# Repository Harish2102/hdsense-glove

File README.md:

<!-- markdownlint-disable MD041 -->

# HDSense Glove

A high-density 32×32 pressure-sensing glove for prosthetics and haptic feedback

*Johns Hopkins University · Advanced Instruments and Systems · Fall 2024*
*Advised by Dr. Nitish Thakor and Arik Slepyan · Neuroengineering and Biomedical Instrumentation Lab*

---

## Overview

The HDSense Glove maps the full tactile surface of a hand using a **32×32 TDMA sensor array** - 1,024 individual pressure points per glove - streaming real-time contact data over serial. Designed for prosthetic hands, robotic manipulation, and human-computer interaction.

**Key specs:**

- 1,024 pressure sensors per glove (32×32 grid)
- **1000 Hz** frame rate, **20ms** latency
- **88% accuracy** detecting objects via compressed sensing
- **18× faster** than traditional raster scanning (Slepyan et al., 2024)
- Teensy 4.1 microcontroller, low-power flex-PCB design

---

## PCB Design

The glove uses a custom flex-PCB shaped to the anatomy of an average male hand (220mm length). Copper traces follow natural glove cuts with a flexible thumb extension. 32 row output pins are driven sequentially via TDMA, with a 5-bit MUX selecting across 32 columns - reducing 1,024 connections to a single analog readout channel.

Left: KiCad flex-PCB layout shaped to the left hand geometry | Right: 32×32 sensor pixel map with finger and palm zones

The PCB was designed in KiCad with separate left-hand (LH) and right-hand (RH) variants. KiCad source files: [`hardware/LH/`](hardware/LH/) and [`hardware/RH/`](hardware/RH/)

---

## Firmware

`firmware/tdma_32x32_foot.ino` - compiled for **Teensy 4.1**

Performs a full 32×32 raster scan per loop using TDMA, outputs all 1,024 values as a comma-separated serial stream per frame. Uses `FASTRUN` and `digitalWriteFast` for maximum scan speed.

```cpp
for (int i = 0; i < 32; i++) {       // activate row
  for (int j = 0; j < 32; j++) {     // step through mux columns
    values[idx++] = analogRead(A0);  // read pressure
  }
}
```

---

## Project Poster

Full project poster - includes KiCad PCB rendering (Fig. 3) and MATLAB sensor heatmap visualization (Fig. 4)

---

## Docs

| Document | Description |
| -------- | ----------- |
| [Final Pitch Deck](docs/HDSense%20Glove%20Final%20Pitch.pdf) | Product pitch and system overview |
| [Project Poster](docs/Harish_Poster_Final.pdf) | Full project summary poster |

---

Harish Balasubramanian · Johns Hopkins University

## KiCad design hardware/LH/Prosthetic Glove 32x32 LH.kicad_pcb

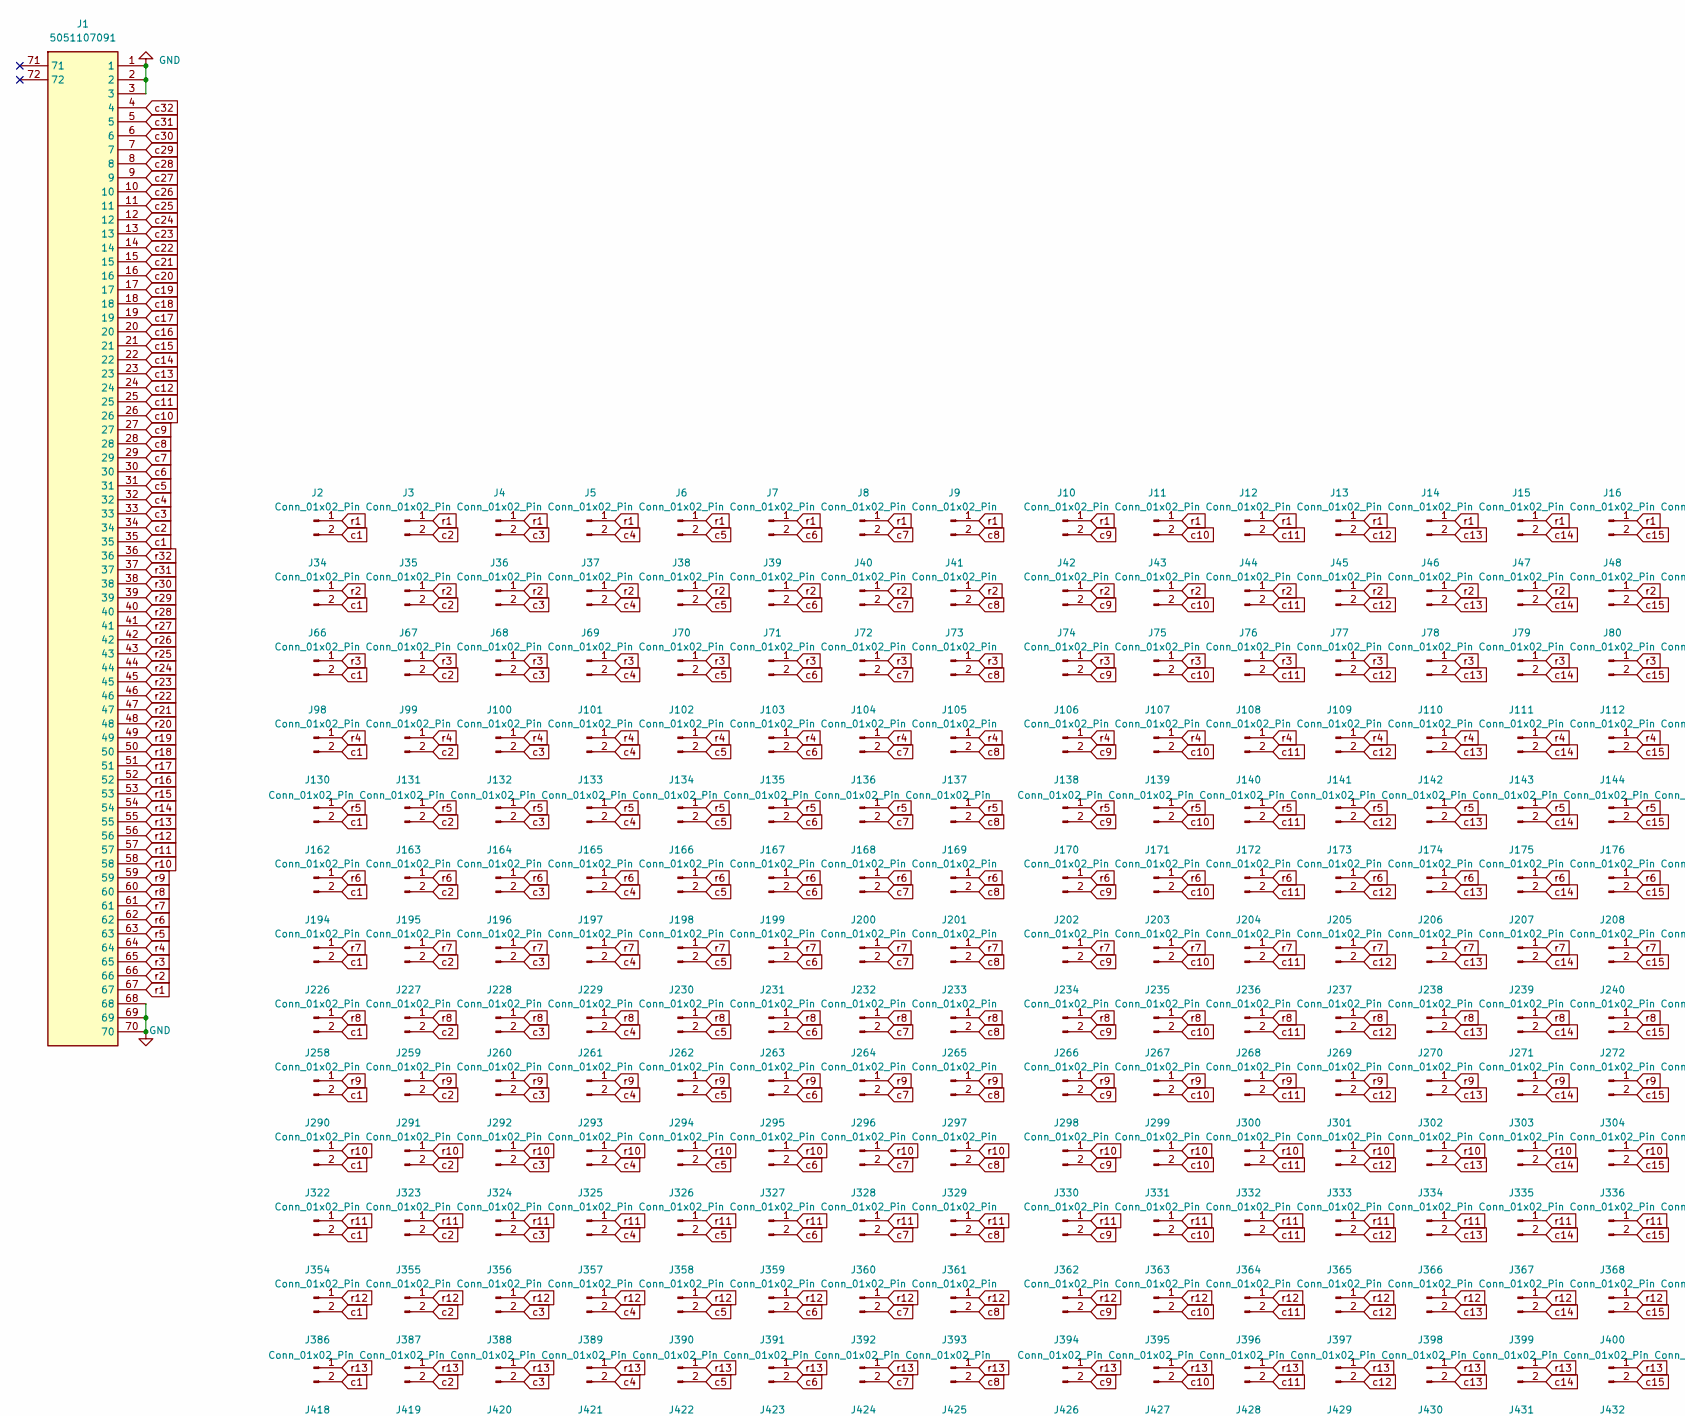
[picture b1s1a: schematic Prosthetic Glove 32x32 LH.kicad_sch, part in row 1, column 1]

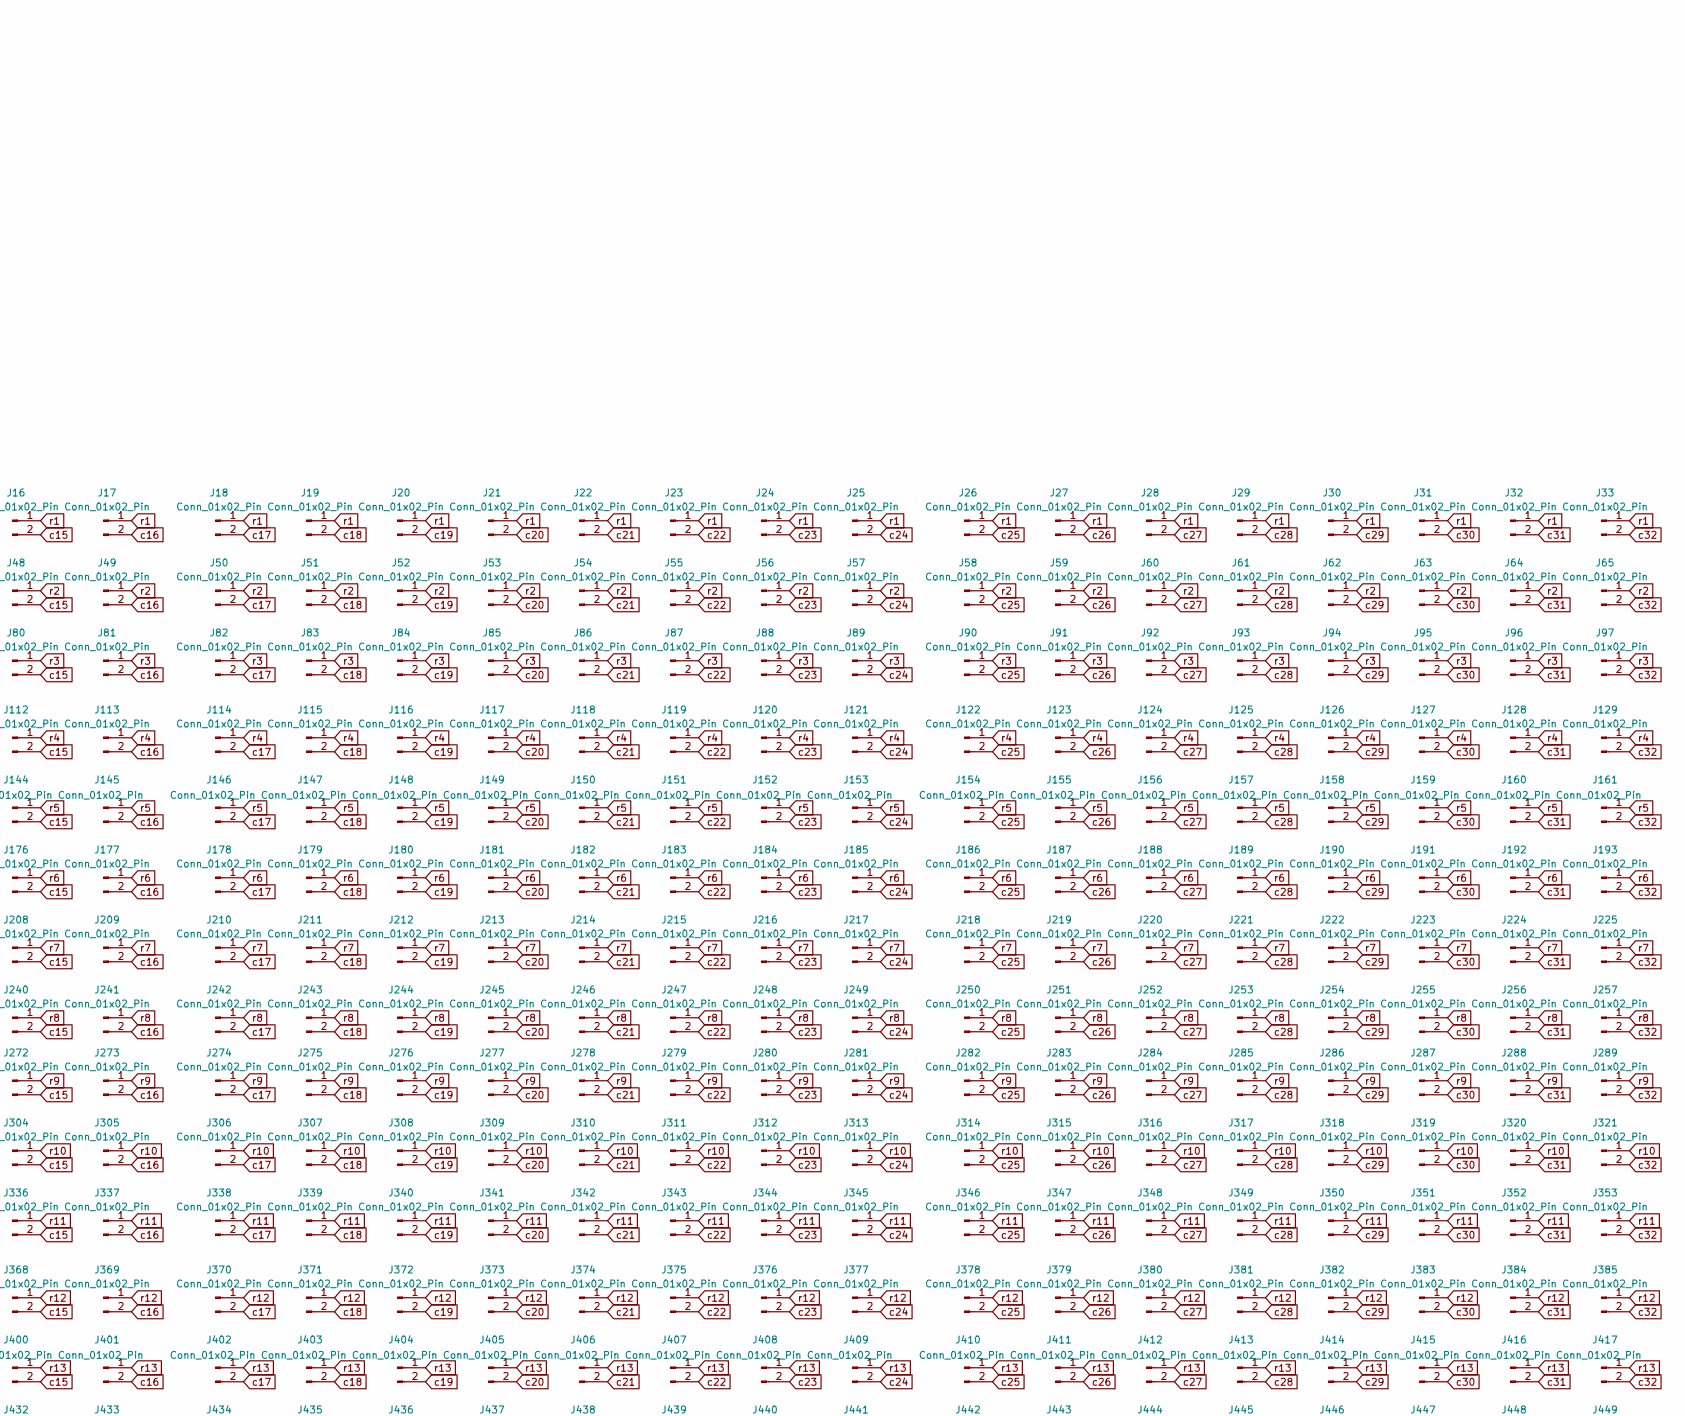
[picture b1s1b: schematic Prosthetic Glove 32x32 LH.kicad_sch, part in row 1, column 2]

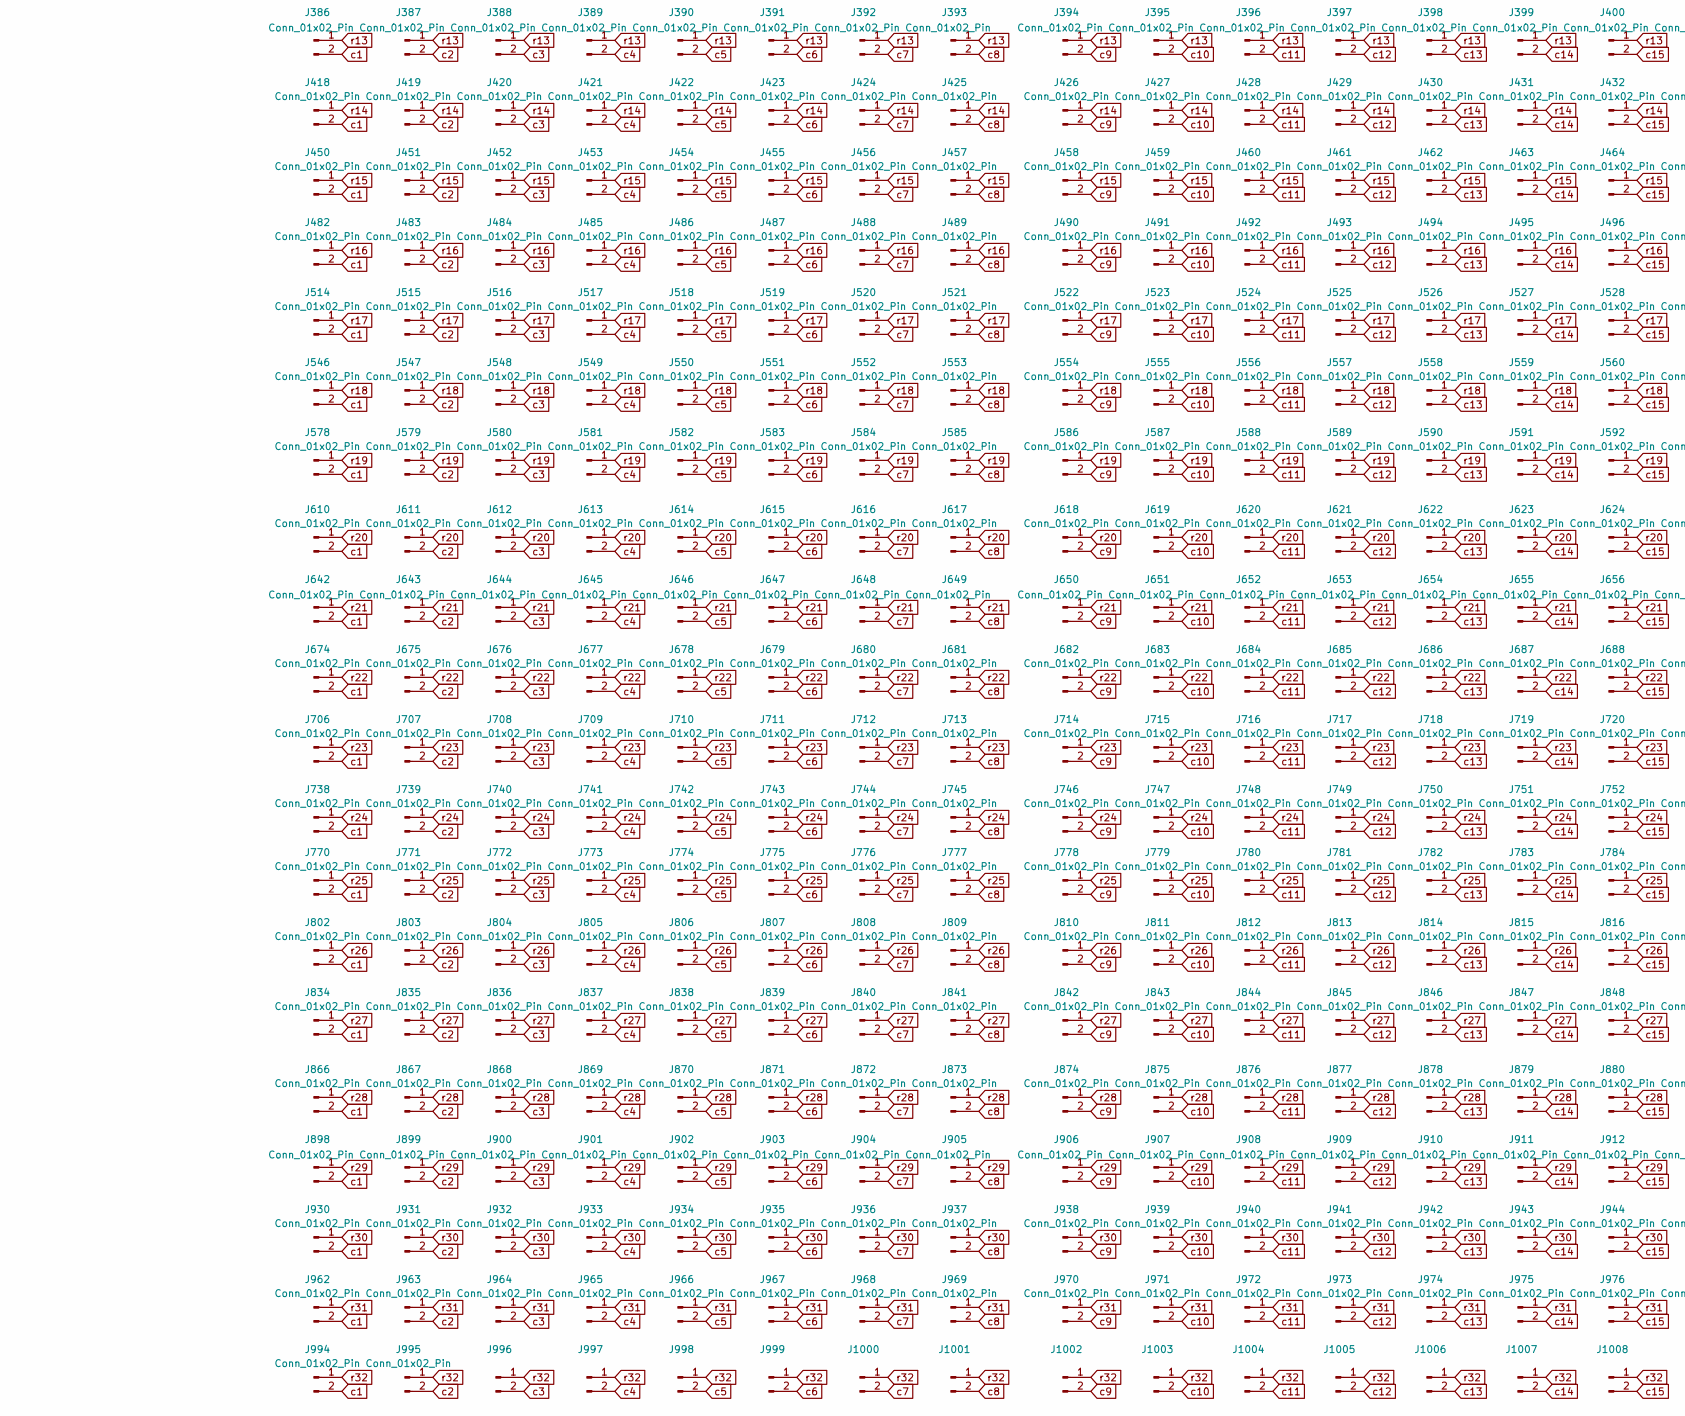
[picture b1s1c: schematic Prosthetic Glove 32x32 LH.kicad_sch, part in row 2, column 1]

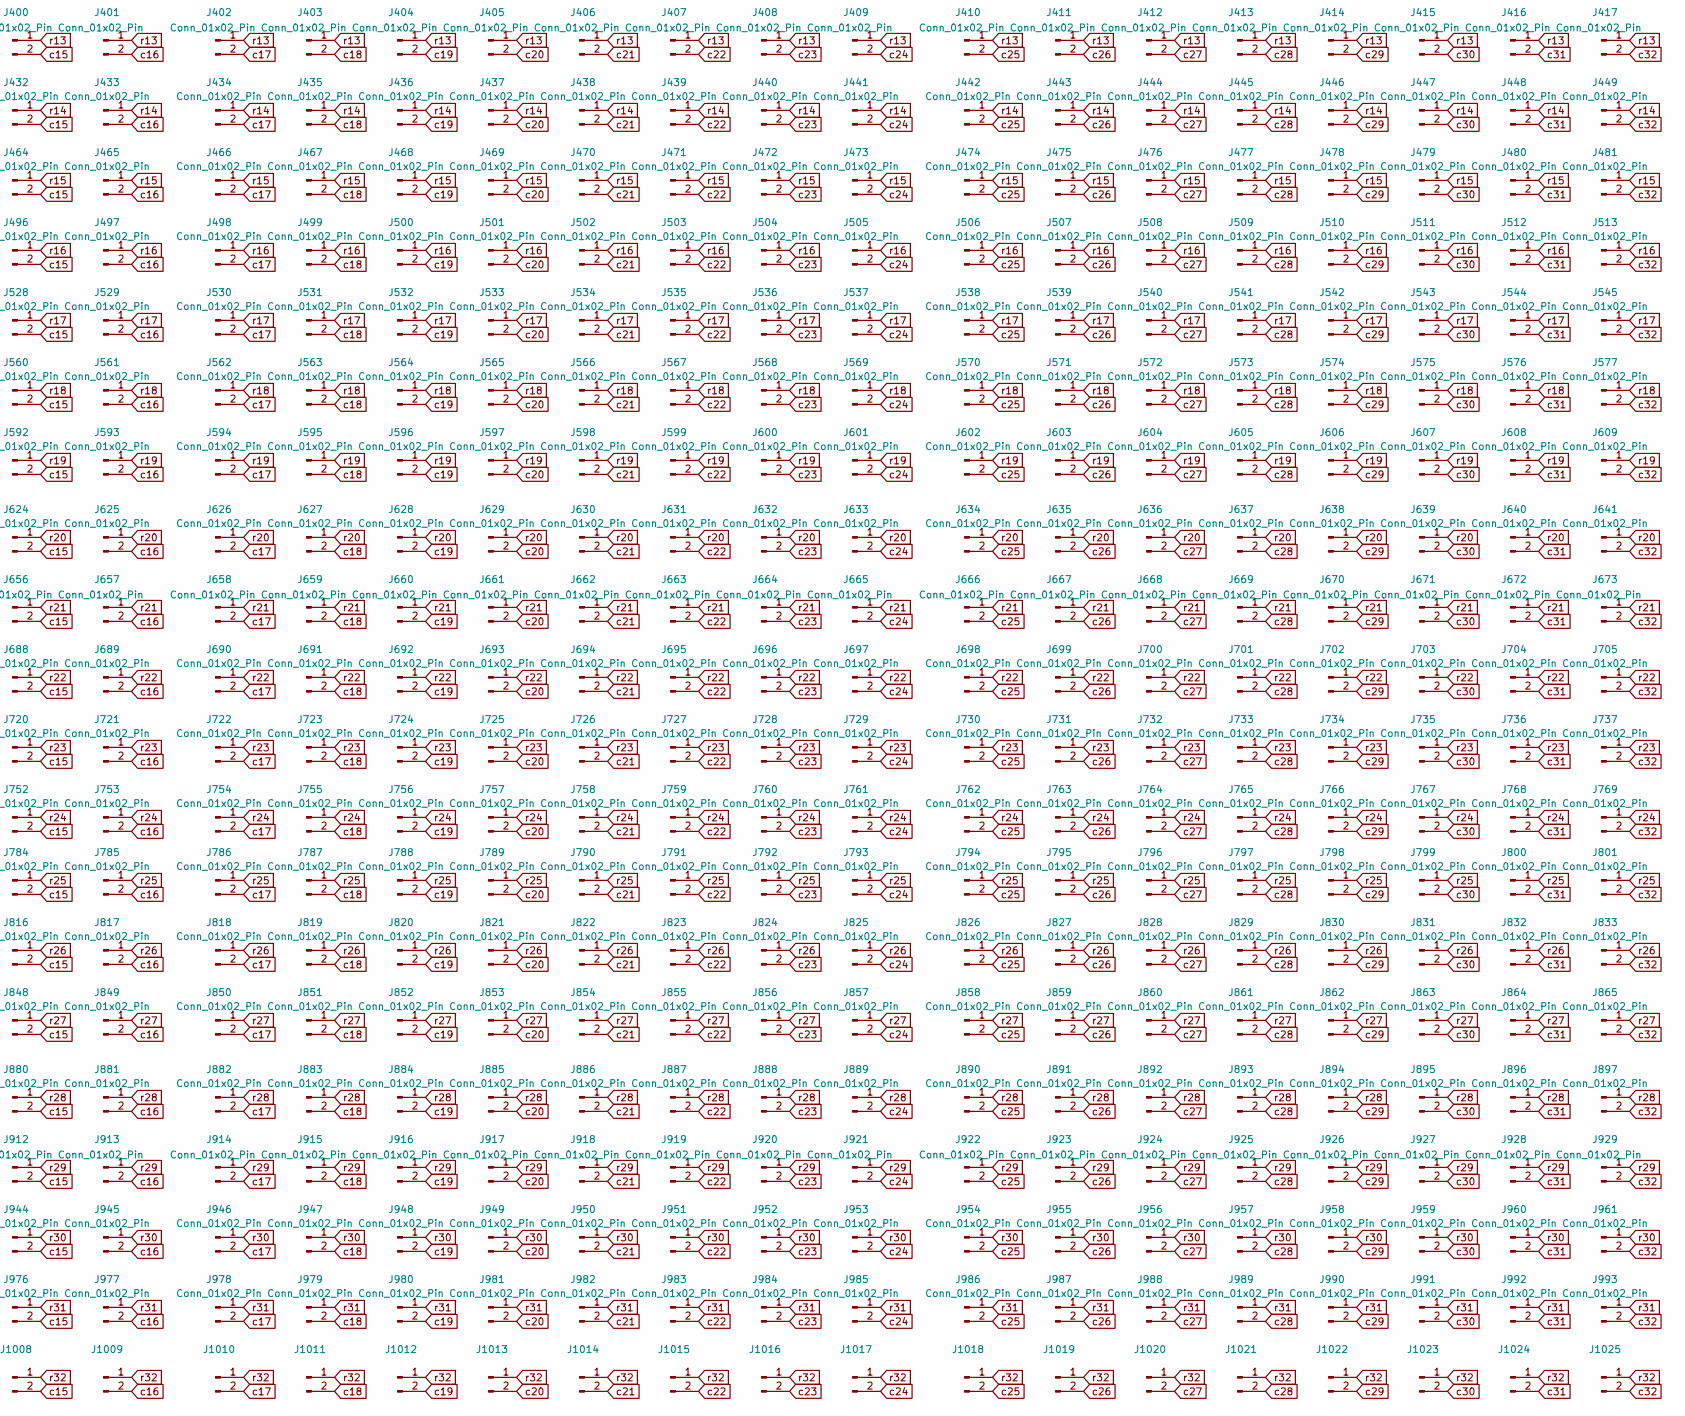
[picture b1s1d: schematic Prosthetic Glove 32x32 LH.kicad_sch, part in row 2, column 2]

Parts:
J1: 5051107091; 70_pos_0.5mm_FPC; Manufacturer_Part_Number 5051107091
J2, J3, J4, J5, J6, J7, J8, J9, J10, J11, J12, J13, J14, J15, J16, J17, J18, J19, J20, J21, J22, J23, J24, J25, J26, J27, J28, J29, J30, J31, J32, J33, J34, J35, J36, J37, J38, J39, J40, J41, J42, J43, J44, J45, J46, J47, J48, J49, J50, J51, J52, J53, J54, J55, J56, J57, J58, J59, J60, J61, J62, J63, J64, J65, J66, J67, J68, J69, J70, J71, J72, J73, J74, J75, J76, J77, J78, J79, J80, J81, J82, J83, J84, J85, J86, J87, J88, J89, J90, J91, J92, J93, J94, J95, J96, J97, J98, J99, J100, J101, J102, J103, J104, J105, J106, J107, J108, J109, J110, J111, J112, J113, J114, J115, J116, J117, J118, J119, J120, J121, J122, J123, J124, J125, J126, J127, J128, J129, J130, J131, J132, J133, J134, J135, J136, J137, J138, J139, J140, J141, J142, J143, J144, J145, J146, J147, J148, J149, J150, J151, J152, J153, J154, J155, J156, J157, J158, J159, J160, J161, J162, J163, J164, J165, J166, J167, J168, J169, J170, J171, J172, J173, J174, J175, J176, J177, J178, J179, J180, J181, J182, J183, J184, J185, J186, J187, J188, J189, J190, J191, J192, J193, J194, J195, J196, J197, J198, J199, J200, J201, J202, J203, J204, J205, J206, J207, J208, J209, J210, J211, J212, J213, J214, J215, J216, J217, J218, J219, J220, J221, J222, J223, J224, J225, J226, J227, J228, J229, J230, J231, J232, J233, J234, J235, J236, J237, J238, J239, J240, J241, J242, J243, J244, J245, J246, J247, J248, J249, J250, J251, J252, J253, J254, J255, J256, J257, J258, J259, J260, J261, J262, J263, J264, J265, J266, J267, J268, J269, J270, J271, J272, J273, J274, J275, J276, J277, J278, J279, J280, J281, J282, J283, J284, J285, J286, J287, J288, J289, J290, J291, J292, J293, J294, J295, J296, J297, J298, J299, J300, J301, J302, J303, J304, J305, J306, J307, J308, J309, J310, J311, J312, J313, J314, J315, J316, J317, J318, J319, J320, J321, J322, J323, J324, J325, J326, J327, J328, J329, J330, J331, J332, J333, J334, J335, J336, J337, J338, J339, J340, J341, J342, J343, J344, J345, J346, J347, J348, J349, J350, J351, J352, J353, J354, J355, J356, J357, J358, J359, J360, J361, J362, J363, J364, J365, J366, J367, J368, J369, J370, J371, J372, J373, J374, J375, J376, J377, J378, J379, J380, J381, J382, J383, J384, J385, J386, J387, J388, J389, J390, J391, J392, J393, J394, J395, J396, J397, J398, J399, J400, J401, J402, J403, J404, J405, J406, J407, J408, J409, J410, J411, J412, J413, J414, J415, J416, J417, J418, J419, J420, J421, J422, J423, J424, J425, J426, J427, J428, J429, J430, J431, J432, J433, J434, J435, J436, J437, J438, J439, J440, J441, J442, J443, J444, J445, J446, J447, J448, J449, J450, J451, J452, J453, J454, J455, J456, J457, J458, J459, J460, J461, J462, J463, J464, J465, J466, J467, J468, J469, J470, J471, J472, J473, J474, J475, J476, J477, J478, J479, J480, J481, J482, J483, J484, J485, J486, J487, J488, J489, J490, J491, J492, J493, J494, J495, J496, J497, J498, J499, J500, J501, J502, J503, J504, J505, J506, J507, J508, J509, J510, J511, J512, J513, J514, J515, J516, J517, J518, J519, J520, J521, J522, J523, J524, J525, J526, J527, J528, J529, J530, J531, J532, J533, J534, J535, J536, J537, J538, J539, J540, J541, J542, J543, J544, J545, J546, J547, J548, J549, J550, J551, J552, J553, J554, J555, J556, J557, J558, J559, J560, J561, J562, J563, J564, J565, J566, J567, J568, J569, J570, J571, J572, J573, J574, J575, J576, J577, J578, J579, J580, J581, J582, J583, J584, J585, J586, J587, J588, J589, J590, J591, J592, J593, J594, J595, J596, J597, J598, J599, J600, J601, J602, J603, J604, J605, J606, J607, J608, J609, J610, J611, J612, J613, J614, J615, J616, J617, J618, J619, J620, J621, J622, J623, J624, J625, J626, J627, J628, J629, J630, J631, J632, J633, J634, J635, J636, J637, J638, J639, J640, J641, J642, J643, J644, J645, J646, J647, J648, J649, J650, J651, J652, J653, J654, J655, J656, J657, J658, J659, J660, J661, J662, J663, J664, J665, J666, J667, J668, J669, J670, J671, J672, J673, J674, J675, J676, J677, J678, J679, J680, J681, J682, J683, J684, J685, J686, J687, J688, J689, J690, J691, J692, J693, J694, J695, J696, J697, J698, J699, J700, J701, J702, J703, J704, J705, J706, J707, J708, J709, J710, J711, J712, J713, J714, J715, J716, J717, J718, J719, J720, J721, J722, J723, J724, J725, J726, J727, J728, J729, J730, J731, J732, J733, J734, J735, J736, J737, J738, J739, J740, J741, J742, J743, J744, J745, J746, J747, J748, J749, J750, J751, J752, J753, J754, J755, J756, J757, J758, J759, J760, J761, J762, J763, J764, J765, J766, J767, J768, J769, J770, J771, J772, J773, J774, J775, J776, J777, J778, J779, J780, J781, J782, J783, J784, J785, J786, J787, J788, J789, J790, J791, J792, J793, J794, J795, J796, J797, J798, J799, J800, J801, J802, J803, J804, J805, J806, J807, J808, J809, J810, J811, J812, J813, J814, J815, J816, J817, J818, J819, J820, J821, J822, J823, J824, J825, J826, J827, J828, J829, J830, J831, J832, J833, J834, J835, J836, J837, J838, J839, J840, J841, J842, J843, J844, J845, J846, J847, J848, J849, J850, J851, J852, J853, J854, J855, J856, J857, J858, J859, J860, J861, J862, J863, J864, J865, J866, J867, J868, J869, J870, J871, J872, J873, J874, J875, J876, J877, J878, J879, J880, J881, J882, J883, J884, J885, J886, J887, J888, J889, J890, J891, J892, J893, J894, J895, J896, J897, J898, J899, J900, J901, J902, J903, J904, J905, J906, J907, J908, J909, J910, J911, J912, J913, J914, J915, J916, J917, J918, J919, J920, J921, J922, J923, J924, J925, J926, J927, J928, J929, J930, J931, J932, J933, J934, J935, J936, J937, J938, J939, J940, J941, J942, J943, J944, J945, J946, J947, J948, J949, J950, J951, J952, J953, J954, J955, J956, J957, J958, J959, J960, J961, J962, J963, J964, J965, J966, J967, J968, J969, J970, J971, J972, J973, J974, J975, J976, J977, J978, J979, J980, J981, J982, J983, J984, J985, J986, J987, J988, J989, J990, J991, J992, J993, J994, J995, J996, J997, J998, J999, J1000, J1001, J1002, J1003, J1004, J1005, J1006, J1007, J1008, J1009, J1010, J1011, J1012, J1013, J1014, J1015, J1016, J1017, J1018, J1019, J1020, J1021, J1022, J1023, J1024, J1025: Conn_01x02_Pin; sensor_2mmx2mm

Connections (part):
GND: J1.1, J1.2, J1.3, J1.68, J1.69, J1.70
c1: J1.35, J2.2, J34.2, J66.2, J98.2, J130.2, J162.2, J194.2, J226.2, J258.2, J290.2, J322.2, J354.2, J386.2, J418.2, J450.2, J482.2, J514.2, J546.2, J578.2, J610.2, J642.2, J674.2, J706.2, J738.2, J770.2, J802.2, J834.2, J866.2, J898.2, J930.2, J962.2, J994.2
c2: J1.34, J3.2, J35.2, J67.2, J99.2, J131.2, J163.2, J195.2, J227.2, J259.2, J291.2, J323.2, J355.2, J387.2, J419.2, J451.2, J483.2, J515.2, J547.2, J579.2, J611.2, J643.2, J675.2, J707.2, J739.2, J771.2, J803.2, J835.2, J867.2, J899.2, J931.2, J963.2, J995.2
c3: J1.33, J4.2, J36.2, J68.2, J100.2, J132.2, J164.2, J196.2, J228.2, J260.2, J292.2, J324.2, J356.2, J388.2, J420.2, J452.2, J484.2, J516.2, J548.2, J580.2, J612.2, J644.2, J676.2, J708.2, J740.2, J772.2, J804.2, J836.2, J868.2, J900.2, J932.2, J964.2, J996.2
c4: J1.32, J5.2, J37.2, J69.2, J101.2, J133.2, J165.2, J197.2, J229.2, J261.2, J293.2, J325.2, J357.2, J389.2, J421.2, J453.2, J485.2, J517.2, J549.2, J581.2, J613.2, J645.2, J677.2, J709.2, J741.2, J773.2, J805.2, J837.2, J869.2, J901.2, J933.2, J965.2, J997.2
c5: J1.31, J6.2, J38.2, J70.2, J102.2, J134.2, J166.2, J198.2, J230.2, J262.2, J294.2, J326.2, J358.2, J390.2, J422.2, J454.2, J486.2, J518.2, J550.2, J582.2, J614.2, J646.2, J678.2, J710.2, J742.2, J774.2, J806.2, J838.2, J870.2, J902.2, J934.2, J966.2, J998.2
c6: J1.30, J7.2, J39.2, J71.2, J103.2, J135.2, J167.2, J199.2, J231.2, J263.2, J295.2, J327.2, J359.2, J391.2, J423.2, J455.2, J487.2, J519.2, J551.2, J583.2, J615.2, J647.2, J679.2, J711.2, J743.2, J775.2, J807.2, J839.2, J871.2, J903.2, J935.2, J967.2, J999.2
c7: J1.29, J8.2, J40.2, J72.2, J104.2, J136.2, J168.2, J200.2, J232.2, J264.2, J296.2, J328.2, J360.2, J392.2, J424.2, J456.2, J488.2, J520.2, J552.2, J584.2, J616.2, J648.2, J680.2, J712.2, J744.2, J776.2, J808.2, J840.2, J872.2, J904.2, J936.2, J968.2, J1000.2
c8: J1.28, J9.2, J41.2, J73.2, J105.2, J137.2, J169.2, J201.2, J233.2, J265.2, J297.2, J329.2, J361.2, J393.2, J425.2, J457.2, J489.2, J521.2, J553.2, J585.2, J617.2, J649.2, J681.2, J713.2, J745.2, J777.2, J809.2, J841.2, J873.2, J905.2, J937.2, J969.2, J1001.2
c9: J1.27, J10.2, J42.2, J74.2, J106.2, J138.2, J170.2, J202.2, J234.2, J266.2, J298.2, J330.2, J362.2, J394.2, J426.2, J458.2, J490.2, J522.2, J554.2, J586.2, J618.2, J650.2, J682.2, J714.2, J746.2, J778.2, J810.2, J842.2, J874.2, J906.2, J938.2, J970.2, J1002.2
c10: J1.26, J11.2, J43.2, J75.2, J107.2, J139.2, J171.2, J203.2, J235.2, J267.2, J299.2, J331.2, J363.2, J395.2, J427.2, J459.2, J491.2, J523.2, J555.2, J587.2, J619.2, J651.2, J683.2, J715.2, J747.2, J779.2, J811.2, J843.2, J875.2, J907.2, J939.2, J971.2, J1003.2
c11: J1.25, J12.2, J44.2, J76.2, J108.2, J140.2, J172.2, J204.2, J236.2, J268.2, J300.2, J332.2, J364.2, J396.2, J428.2, J460.2, J492.2, J524.2, J556.2, J588.2, J620.2, J652.2, J684.2, J716.2, J748.2, J780.2, J812.2, J844.2, J876.2, J908.2, J940.2, J972.2, J1004.2
c12: J1.24, J13.2, J45.2, J77.2, J109.2, J141.2, J173.2, J205.2, J237.2, J269.2, J301.2, J333.2, J365.2, J397.2, J429.2, J461.2, J493.2, J525.2, J557.2, J589.2, J621.2, J653.2, J685.2, J717.2, J749.2, J781.2, J813.2, J845.2, J877.2, J909.2, J941.2, J973.2, J1005.2
c13: J1.23, J14.2, J46.2, J78.2, J110.2, J142.2, J174.2, J206.2, J238.2, J270.2, J302.2, J334.2, J366.2, J398.2, J430.2, J462.2, J494.2, J526.2, J558.2, J590.2, J622.2, J654.2, J686.2, J718.2, J750.2, J782.2, J814.2, J846.2, J878.2, J910.2, J942.2, J974.2, J1006.2
c14: J1.22, J15.2, J47.2, J79.2, J111.2, J143.2, J175.2, J207.2, J239.2, J271.2, J303.2, J335.2, J367.2, J399.2, J431.2, J463.2, J495.2, J527.2, J559.2, J591.2, J623.2, J655.2, J687.2, J719.2, J751.2, J783.2, J815.2, J847.2, J879.2, J911.2, J943.2, J975.2, J1007.2
c15: J1.21, J16.2, J48.2, J80.2, J112.2, J144.2, J176.2, J208.2, J240.2, J272.2, J304.2, J336.2, J368.2, J400.2, J432.2, J464.2, J496.2, J528.2, J560.2, J592.2, J624.2, J656.2, J688.2, J720.2, J752.2, J784.2, J816.2, J848.2, J880.2, J912.2, J944.2, J976.2, J1008.2
c16: J1.20, J17.2, J49.2, J81.2, J113.2, J145.2, J177.2, J209.2, J241.2, J273.2, J305.2, J337.2, J369.2, J401.2, J433.2, J465.2, J497.2, J529.2, J561.2, J593.2, J625.2, J657.2, J689.2, J721.2, J753.2, J785.2, J817.2, J849.2, J881.2, J913.2, J945.2, J977.2, J1009.2
c17: J1.19, J18.2, J50.2, J82.2, J114.2, J146.2, J178.2, J210.2, J242.2, J274.2, J306.2, J338.2, J370.2, J402.2, J434.2, J466.2, J498.2, J530.2, J562.2, J594.2, J626.2, J658.2, J690.2, J722.2, J754.2, J786.2, J818.2, J850.2, J882.2, J914.2, J946.2, J978.2, J1010.2
c18: J1.18, J19.2, J51.2, J83.2, J115.2, J147.2, J179.2, J211.2, J243.2, J275.2, J307.2, J339.2, J371.2, J403.2, J435.2, J467.2, J499.2, J531.2, J563.2, J595.2, J627.2, J659.2, J691.2, J723.2, J755.2, J787.2, J819.2, J851.2, J883.2, J915.2, J947.2, J979.2, J1011.2
c19: J1.17, J20.2, J52.2, J84.2, J116.2, J148.2, J180.2, J212.2, J244.2, J276.2, J308.2, J340.2, J372.2, J404.2, J436.2, J468.2, J500.2, J532.2, J564.2, J596.2, J628.2, J660.2, J692.2, J724.2, J756.2, J788.2, J820.2, J852.2, J884.2, J916.2, J948.2, J980.2, J1012.2
c20: J1.16, J21.2, J53.2, J85.2, J117.2, J149.2, J181.2, J213.2, J245.2, J277.2, J309.2, J341.2, J373.2, J405.2, J437.2, J469.2, J501.2, J533.2, J565.2, J597.2, J629.2, J661.2, J693.2, J725.2, J757.2, J789.2, J821.2, J853.2, J885.2, J917.2, J949.2, J981.2, J1013.2
c21: J1.15, J22.2, J54.2, J86.2, J118.2, J150.2, J182.2, J214.2, J246.2, J278.2, J310.2, J342.2, J374.2, J406.2, J438.2, J470.2, J502.2, J534.2, J566.2, J598.2, J630.2, J662.2, J694.2, J726.2, J758.2, J790.2, J822.2, J854.2, J886.2, J918.2, J950.2, J982.2, J1014.2
c22: J1.14, J23.2, J55.2, J87.2, J119.2, J151.2, J183.2, J215.2, J247.2, J279.2, J311.2, J343.2, J375.2, J407.2, J439.2, J471.2, J503.2, J535.2, J567.2, J599.2, J631.2, J663.2, J695.2, J727.2, J759.2, J791.2, J823.2, J855.2, J887.2, J919.2, J951.2, J983.2, J1015.2
c23: J1.13, J24.2, J56.2, J88.2, J120.2, J152.2, J184.2, J216.2, J248.2, J280.2, J312.2, J344.2, J376.2, J408.2, J440.2, J472.2, J504.2, J536.2, J568.2, J600.2, J632.2, J664.2, J696.2, J728.2, J760.2, J792.2, J824.2, J856.2, J888.2, J920.2, J952.2, J984.2, J1016.2
c24: J1.12, J25.2, J57.2, J89.2, J121.2, J153.2, J185.2, J217.2, J249.2, J281.2, J313.2, J345.2, J377.2, J409.2, J441.2, J473.2, J505.2, J537.2, J569.2, J601.2, J633.2, J665.2, J697.2, J729.2, J761.2, J793.2, J825.2, J857.2, J889.2, J921.2, J953.2, J985.2, J1017.2
c25: J1.11, J26.2, J58.2, J90.2, J122.2, J154.2, J186.2, J218.2, J250.2, J282.2, J314.2, J346.2, J378.2, J410.2, J442.2, J474.2, J506.2, J538.2, J570.2, J602.2, J634.2, J666.2, J698.2, J730.2, J762.2, J794.2, J826.2, J858.2, J890.2, J922.2, J954.2, J986.2, J1018.2
c26: J1.10, J27.2, J59.2, J91.2, J123.2, J155.2, J187.2, J219.2, J251.2, J283.2, J315.2, J347.2, J379.2, J411.2, J443.2, J475.2, J507.2, J539.2, J571.2, J603.2, J635.2, J667.2, J699.2, J731.2, J763.2, J795.2, J827.2, J859.2, J891.2, J923.2, J955.2, J987.2, J1019.2
c27: J1.9, J28.2, J60.2, J92.2, J124.2, J156.2, J188.2, J220.2, J252.2, J284.2, J316.2, J348.2, J380.2, J412.2, J444.2, J476.2, J508.2, J540.2, J572.2, J604.2, J636.2, J668.2, J700.2, J732.2, J764.2, J796.2, J828.2, J860.2, J892.2, J924.2, J956.2, J988.2, J1020.2
c28: J1.8, J29.2, J61.2, J93.2, J125.2, J157.2, J189.2, J221.2, J253.2, J285.2, J317.2, J349.2, J381.2, J413.2, J445.2, J477.2, J509.2, J541.2, J573.2, J605.2, J637.2, J669.2, J701.2, J733.2, J765.2, J797.2, J829.2, J861.2, J893.2, J925.2, J957.2, J989.2, J1021.2
c29: J1.7, J30.2, J62.2, J94.2, J126.2, J158.2, J190.2, J222.2, J254.2, J286.2, J318.2, J350.2, J382.2, J414.2, J446.2, J478.2, J510.2, J542.2, J574.2, J606.2, J638.2, J670.2, J702.2, J734.2, J766.2, J798.2, J830.2, J862.2, J894.2, J926.2, J958.2, J990.2, J1022.2
c30: J1.6, J31.2, J63.2, J95.2, J127.2, J159.2, J191.2, J223.2, J255.2, J287.2, J319.2, J351.2, J383.2, J415.2, J447.2, J479.2, J511.2, J543.2, J575.2, J607.2, J639.2, J671.2, J703.2, J735.2, J767.2, J799.2, J831.2, J863.2, J895.2, J927.2, J959.2, J991.2, J1023.2
c31: J1.5, J32.2, J64.2, J96.2, J128.2, J160.2, J192.2, J224.2, J256.2, J288.2, J320.2, J352.2, J384.2, J416.2, J448.2, J480.2, J512.2, J544.2, J576.2, J608.2, J640.2, J672.2, J704.2, J736.2, J768.2, J800.2, J832.2, J864.2, J896.2, J928.2, J960.2, J992.2, J1024.2
c32: J1.4, J33.2, J65.2, J97.2, J129.2, J161.2, J193.2, J225.2, J257.2, J289.2, J321.2, J353.2, J385.2, J417.2, J449.2, J481.2, J513.2, J545.2, J577.2, J609.2, J641.2, J673.2, J705.2, J737.2, J769.2, J801.2, J833.2, J865.2, J897.2, J929.2, J961.2, J993.2, J1025.2
r1: J1.67, J2.1, J3.1, J4.1, J5.1, J6.1, J7.1, J8.1, J9.1, J10.1, J11.1, J12.1, J13.1, J14.1, J15.1, J16.1, J17.1, J18.1, J19.1, J20.1, J21.1, J22.1, J23.1, J24.1, J25.1, J26.1, J27.1, J28.1, J29.1, J30.1, J31.1, J32.1, J33.1
r2: J1.66, J34.1, J35.1, J36.1, J37.1, J38.1, J39.1, J40.1, J41.1, J42.1, J43.1, J44.1, J45.1, J46.1, J47.1, J48.1, J49.1, J50.1, J51.1, J52.1, J53.1, J54.1, J55.1, J56.1, J57.1, J58.1, J59.1, J60.1, J61.1, J62.1, J63.1, J64.1, J65.1
r3: J1.65, J66.1, J67.1, J68.1, J69.1, J70.1, J71.1, J72.1, J73.1, J74.1, J75.1, J76.1, J77.1, J78.1, J79.1, J80.1, J81.1, J82.1, J83.1, J84.1, J85.1, J86.1, J87.1, J88.1, J89.1, J90.1, J91.1, J92.1, J93.1, J94.1, J95.1, J96.1, J97.1
r4: J1.64, J98.1, J99.1, J100.1, J101.1, J102.1, J103.1, J104.1, J105.1, J106.1, J107.1, J108.1, J109.1, J110.1, J111.1, J112.1, J113.1, J114.1, J115.1, J116.1, J117.1, J118.1, J119.1, J120.1, J121.1, J122.1, J123.1, J124.1, J125.1, J126.1, J127.1, J128.1, J129.1
r5: J1.63, J130.1, J131.1, J132.1, J133.1, J134.1, J135.1, J136.1, J137.1, J138.1, J139.1, J140.1, J141.1, J142.1, J143.1, J144.1, J145.1, J146.1, J147.1, J148.1, J149.1, J150.1, J151.1, J152.1, J153.1, J154.1, J155.1, J156.1, J157.1, J158.1, J159.1, J160.1, J161.1
r6: J1.62, J162.1, J163.1, J164.1, J165.1, J166.1, J167.1, J168.1, J169.1, J170.1, J171.1, J172.1, J173.1, J174.1, J175.1, J176.1, J177.1, J178.1, J179.1, J180.1, J181.1, J182.1, J183.1, J184.1, J185.1, J186.1, J187.1, J188.1, J189.1, J190.1, J191.1, J192.1, J193.1
r7: J1.61, J194.1, J195.1, J196.1, J197.1, J198.1, J199.1, J200.1, J201.1, J202.1, J203.1, J204.1, J205.1, J206.1, J207.1, J208.1, J209.1, J210.1, J211.1, J212.1, J213.1, J214.1, J215.1, J216.1, J217.1, J218.1, J219.1, J220.1, J221.1, J222.1, J223.1, J224.1, J225.1
r8: J1.60, J226.1, J227.1, J228.1, J229.1, J230.1, J231.1, J232.1, J233.1, J234.1, J235.1, J236.1, J237.1, J238.1, J239.1, J240.1, J241.1, J242.1, J243.1, J244.1, J245.1, J246.1, J247.1, J248.1, J249.1, J250.1, J251.1, J252.1, J253.1, J254.1, J255.1, J256.1, J257.1
r9: J1.59, J258.1, J259.1, J260.1, J261.1, J262.1, J263.1, J264.1, J265.1, J266.1, J267.1, J268.1, J269.1, J270.1, J271.1, J272.1, J273.1, J274.1, J275.1, J276.1, J277.1, J278.1, J279.1, J280.1, J281.1, J282.1, J283.1, J284.1, J285.1, J286.1, J287.1, J288.1, J289.1
r10: J1.58, J290.1, J291.1, J292.1, J293.1, J294.1, J295.1, J296.1, J297.1, J298.1, J299.1, J300.1, J301.1, J302.1, J303.1, J304.1, J305.1, J306.1, J307.1, J308.1, J309.1, J310.1, J311.1, J312.1, J313.1, J314.1, J315.1, J316.1, J317.1, J318.1, J319.1, J320.1, J321.1
r11: J1.57, J322.1, J323.1, J324.1, J325.1, J326.1, J327.1, J328.1, J329.1, J330.1, J331.1, J332.1, J333.1, J334.1, J335.1, J336.1, J337.1, J338.1, J339.1, J340.1, J341.1, J342.1, J343.1, J344.1, J345.1, J346.1, J347.1, J348.1, J349.1, J350.1, J351.1, J352.1, J353.1
r12: J1.56, J354.1, J355.1, J356.1, J357.1, J358.1, J359.1, J360.1, J361.1, J362.1, J363.1, J364.1, J365.1, J366.1, J367.1, J368.1, J369.1, J370.1, J371.1, J372.1, J373.1, J374.1, J375.1, J376.1, J377.1, J378.1, J379.1, J380.1, J381.1, J382.1, J383.1, J384.1, J385.1
r13: J1.55, J386.1, J387.1, J388.1, J389.1, J390.1, J391.1, J392.1, J393.1, J394.1, J395.1, J396.1, J397.1, J398.1, J399.1, J400.1, J401.1, J402.1, J403.1, J404.1, J405.1, J406.1, J407.1, J408.1, J409.1, J410.1, J411.1, J412.1, J413.1, J414.1, J415.1, J416.1, J417.1
r14: J1.54, J418.1, J419.1, J420.1, J421.1, J422.1, J423.1, J424.1, J425.1, J426.1, J427.1, J428.1, J429.1, J430.1, J431.1, J432.1, J433.1, J434.1, J435.1, J436.1, J437.1, J438.1, J439.1, J440.1, J441.1, J442.1, J443.1, J444.1, J445.1, J446.1, J447.1, J448.1, J449.1
r15: J1.53, J450.1, J451.1, J452.1, J453.1, J454.1, J455.1, J456.1, J457.1, J458.1, J459.1, J460.1, J461.1, J462.1, J463.1, J464.1, J465.1, J466.1, J467.1, J468.1, J469.1, J470.1, J471.1, J472.1, J473.1, J474.1, J475.1, J476.1, J477.1, J478.1, J479.1, J480.1, J481.1
r16: J1.52, J482.1, J483.1, J484.1, J485.1, J486.1, J487.1, J488.1, J489.1, J490.1, J491.1, J492.1, J493.1, J494.1, J495.1, J496.1, J497.1, J498.1, J499.1, J500.1, J501.1, J502.1, J503.1, J504.1, J505.1, J506.1, J507.1, J508.1, J509.1, J510.1, J511.1, J512.1, J513.1
r17: J1.51, J514.1, J515.1, J516.1, J517.1, J518.1, J519.1, J520.1, J521.1, J522.1, J523.1, J524.1, J525.1, J526.1, J527.1, J528.1, J529.1, J530.1, J531.1, J532.1, J533.1, J534.1, J535.1, J536.1, J537.1, J538.1, J539.1, J540.1, J541.1, J542.1, J543.1, J544.1, J545.1
r18: J1.50, J546.1, J547.1, J548.1, J549.1, J550.1, J551.1, J552.1, J553.1, J554.1, J555.1, J556.1, J557.1, J558.1, J559.1, J560.1, J561.1, J562.1, J563.1, J564.1, J565.1, J566.1, J567.1, J568.1, J569.1, J570.1, J571.1, J572.1, J573.1, J574.1, J575.1, J576.1, J577.1
r19: J1.49, J578.1, J579.1, J580.1, J581.1, J582.1, J583.1, J584.1, J585.1, J586.1, J587.1, J588.1, J589.1, J590.1, J591.1, J592.1, J593.1, J594.1, J595.1, J596.1, J597.1, J598.1, J599.1, J600.1, J601.1, J602.1, J603.1, J604.1, J605.1, J606.1, J607.1, J608.1, J609.1
r20: J1.48, J610.1, J611.1, J612.1, J613.1, J614.1, J615.1, J616.1, J617.1, J618.1, J619.1, J620.1, J621.1, J622.1, J623.1, J624.1, J625.1, J626.1, J627.1, J628.1, J629.1, J630.1, J631.1, J632.1, J633.1, J634.1, J635.1, J636.1, J637.1, J638.1, J639.1, J640.1, J641.1
r21: J1.47, J642.1, J643.1, J644.1, J645.1, J646.1, J647.1, J648.1, J649.1, J650.1, J651.1, J652.1, J653.1, J654.1, J655.1, J656.1, J657.1, J658.1, J659.1, J660.1, J661.1, J662.1, J663.1, J664.1, J665.1, J666.1, J667.1, J668.1, J669.1, J670.1, J671.1, J672.1, J673.1
r22: J1.46, J674.1, J675.1, J676.1, J677.1, J678.1, J679.1, J680.1, J681.1, J682.1, J683.1, J684.1, J685.1, J686.1, J687.1, J688.1, J689.1, J690.1, J691.1, J692.1, J693.1, J694.1, J695.1, J696.1, J697.1, J698.1, J699.1, J700.1, J701.1, J702.1, J703.1, J704.1, J705.1
r23: J1.45, J706.1, J707.1, J708.1, J709.1, J710.1, J711.1, J712.1, J713.1, J714.1, J715.1, J716.1, J717.1, J718.1, J719.1, J720.1, J721.1, J722.1, J723.1, J724.1, J725.1, J726.1, J727.1, J728.1, J729.1, J730.1, J731.1, J732.1, J733.1, J734.1, J735.1, J736.1, J737.1
r24: J1.44, J738.1, J739.1, J740.1, J741.1, J742.1, J743.1, J744.1, J745.1, J746.1, J747.1, J748.1, J749.1, J750.1, J751.1, J752.1, J753.1, J754.1, J755.1, J756.1, J757.1, J758.1, J759.1, J760.1, J761.1, J762.1, J763.1, J764.1, J765.1, J766.1, J767.1, J768.1, J769.1
r25: J1.43, J770.1, J771.1, J772.1, J773.1, J774.1, J775.1, J776.1, J777.1, J778.1, J779.1, J780.1, J781.1, J782.1, J783.1, J784.1, J785.1, J786.1, J787.1, J788.1, J789.1, J790.1, J791.1, J792.1, J793.1, J794.1, J795.1, J796.1, J797.1, J798.1, J799.1, J800.1, J801.1
r26: J1.42, J802.1, J803.1, J804.1, J805.1, J806.1, J807.1, J808.1, J809.1, J810.1, J811.1, J812.1, J813.1, J814.1, J815.1, J816.1, J817.1, J818.1, J819.1, J820.1, J821.1, J822.1, J823.1, J824.1, J825.1, J826.1, J827.1, J828.1, J829.1, J830.1, J831.1, J832.1, J833.1
r27: J1.41, J834.1, J835.1, J836.1, J837.1, J838.1, J839.1, J840.1, J841.1, J842.1, J843.1, J844.1, J845.1, J846.1, J847.1, J848.1, J849.1, J850.1, J851.1, J852.1, J853.1, J854.1, J855.1, J856.1, J857.1, J858.1, J859.1, J860.1, J861.1, J862.1, J863.1, J864.1, J865.1
r28: J1.40, J866.1, J867.1, J868.1, J869.1, J870.1, J871.1, J872.1, J873.1, J874.1, J875.1, J876.1, J877.1, J878.1, J879.1, J880.1, J881.1, J882.1, J883.1, J884.1, J885.1, J886.1, J887.1, J888.1, J889.1, J890.1, J891.1, J892.1, J893.1, J894.1, J895.1, J896.1, J897.1
r29: J1.39, J898.1, J899.1, J900.1, J901.1, J902.1, J903.1, J904.1, J905.1, J906.1, J907.1, J908.1, J909.1, J910.1, J911.1, J912.1, J913.1, J914.1, J915.1, J916.1, J917.1, J918.1, J919.1, J920.1, J921.1, J922.1, J923.1, J924.1, J925.1, J926.1, J927.1, J928.1, J929.1
r30: J1.38, J930.1, J931.1, J932.1, J933.1, J934.1, J935.1, J936.1, J937.1, J938.1, J939.1, J940.1, J941.1, J942.1, J943.1, J944.1, J945.1, J946.1, J947.1, J948.1, J949.1, J950.1, J951.1, J952.1, J953.1, J954.1, J955.1, J956.1, J957.1, J958.1, J959.1, J960.1, J961.1
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
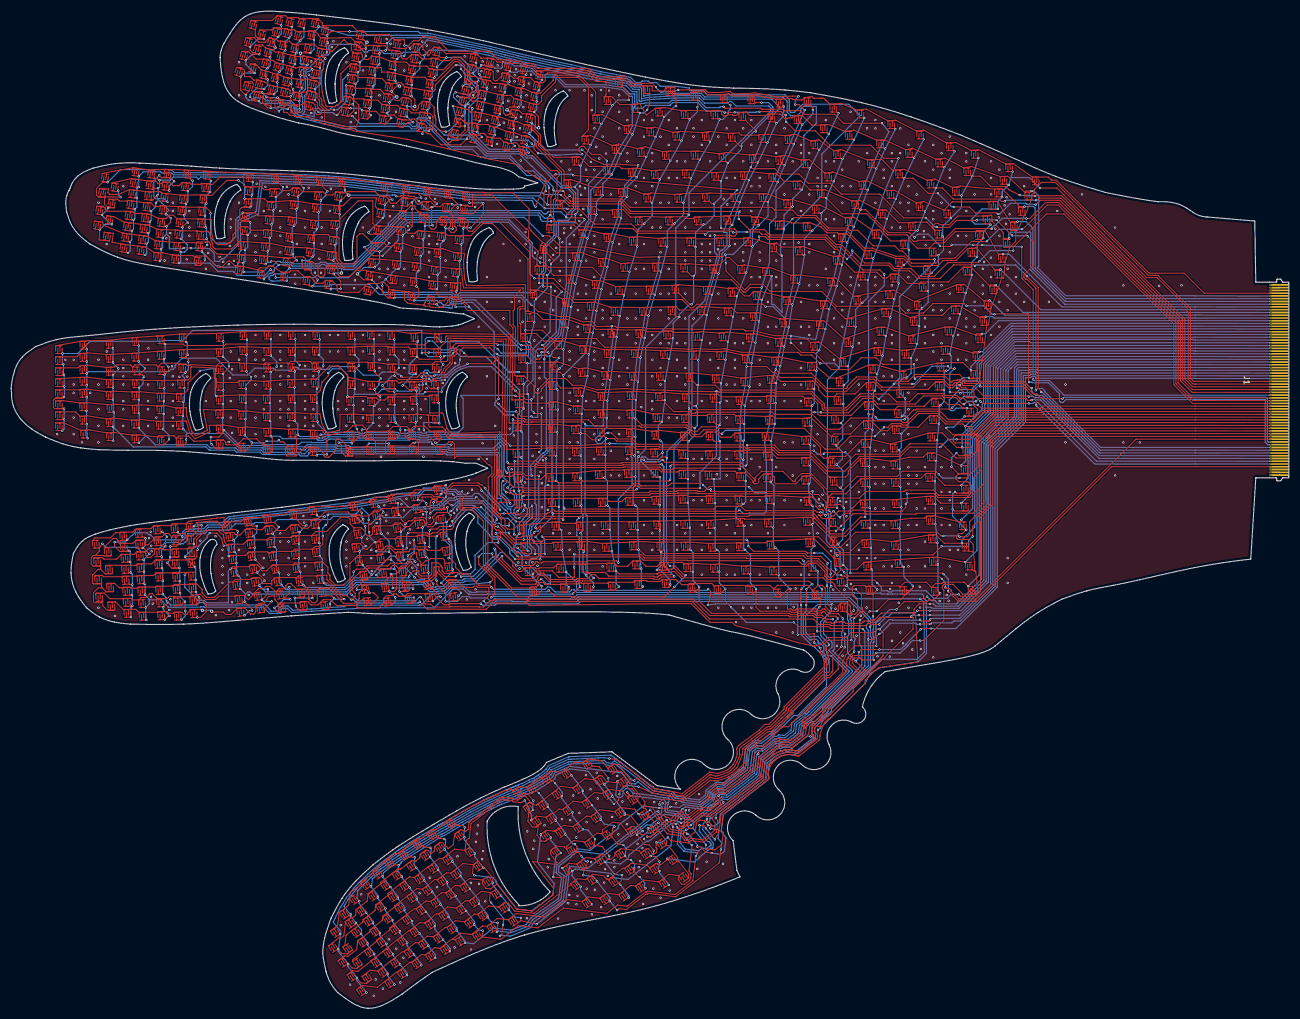
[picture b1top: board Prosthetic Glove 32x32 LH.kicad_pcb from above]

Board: 2 copper layers, 231.9 x 181.0 mm, 1025 parts (0 on the bottom side), 65 nets.
